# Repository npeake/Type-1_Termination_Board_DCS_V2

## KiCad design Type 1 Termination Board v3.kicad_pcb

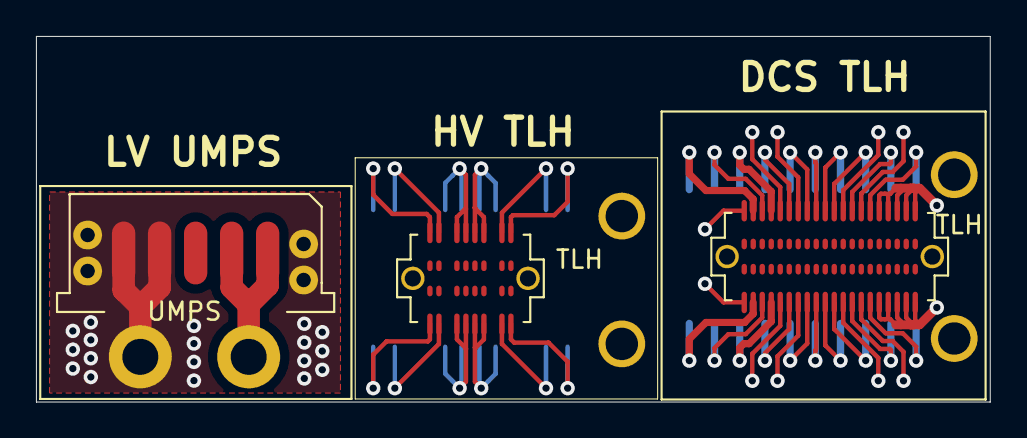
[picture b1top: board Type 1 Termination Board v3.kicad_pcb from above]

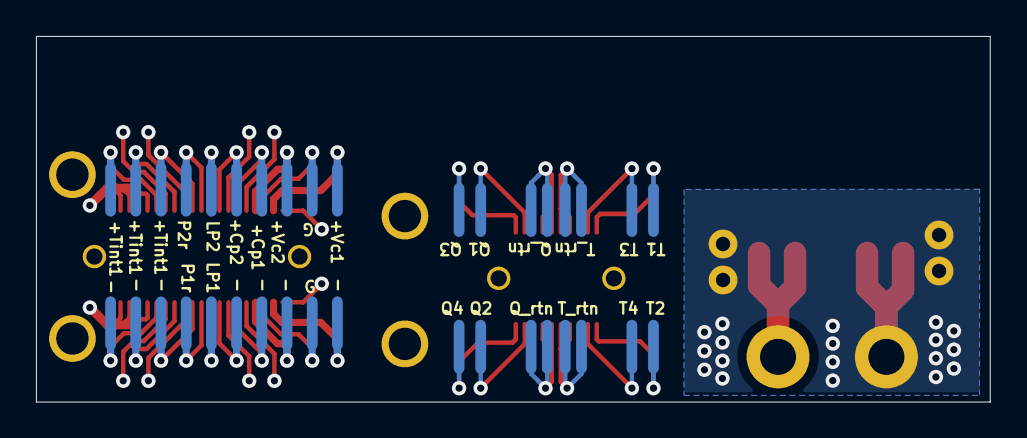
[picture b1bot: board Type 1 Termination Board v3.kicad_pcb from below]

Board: 4 copper layers, 53.0 x 20.3 mm, 13 parts (4 on the bottom side), 3 nets.

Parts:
J2, J3: Conn_01x01_Female; 14AWG_THT
J10: UMPS; UMPS 5 Pin
J11: TLH; 19-1_TLH_HV
J12: TLH; TLH 20 Pin
J20, J21, J22, J23: PEEK_screw
P1, P2, P3, P4: Pad_Array_2

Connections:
/LV: J2.1, J10.1, J10.2
/return: J3.1, J10.4, J10.5, J10.6, J10.7, J10.8, J10.9
GND: J10.3, J12.1, J12.2, J12.5, J12.6, J12.9, J12.10, J12.13, J12.14, J12.19, J12.20, J12.23, J12.24, J12.27, J12.28, J12.31, J12.32, J12.33, J12.34, J12.35, J12.36, J12.37, J12.38, J12.39, J12.40, J12.41, J12.42, J22.43, J23.44, P1.6, P1.20, P2.5, P2.19

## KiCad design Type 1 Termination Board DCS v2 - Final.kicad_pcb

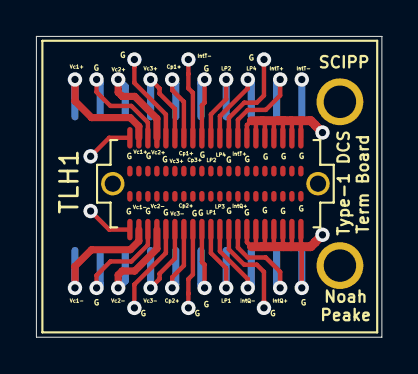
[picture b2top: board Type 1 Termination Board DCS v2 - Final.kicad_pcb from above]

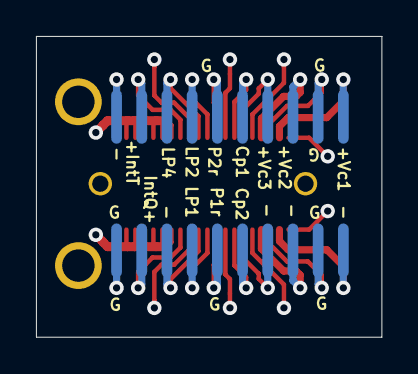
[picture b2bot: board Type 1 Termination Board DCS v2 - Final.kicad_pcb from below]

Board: 4 copper layers, 19.2 x 16.7 mm, 5 parts (2 on the bottom side), 16 nets.

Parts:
J22, J23: PEEK_screw
P1, P2: Pad_Array_2
TLH1: Conn_02x20_Odd_Even; TLH 20 Pin

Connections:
Can_pwr1: P2.15, TLH1.13
Can_pwr2: P1.16, TLH1.14
Can_pwr3: P2.29, TLH1.15
Gnd: J22.43, J23.44, P1.6, P1.18, P1.30, P2.5, P2.17, TLH1.1, TLH1.2, TLH1.5, TLH1.6, TLH1.9, TLH1.10, TLH1.16, TLH1.17, TLH1.18, TLH1.23, TLH1.24, TLH1.27, TLH1.28, TLH1.29, TLH1.30, TLH1.31, TLH1.32, TLH1.33, TLH1.34, TLH1.35, TLH1.36, TLH1.37, TLH1.38, TLH1.39, TLH1.40
Interlock_Q+: P1.26, TLH1.26
Interlock_T+: P2.25, TLH1.25
LP_mode1: P1.20, TLH1.20
LP_mode2: P2.19, TLH1.19
LP_mode3: P1.22, TLH1.22
LP_mode4: P2.21, TLH1.21
Vcan1+: P2.3, TLH1.3
Vcan1-: P1.4, TLH1.4
Vcan2+: P2.7, TLH1.7
Vcan2-: P1.8, TLH1.8
Vcan3+: P2.11, TLH1.11
Vcan3-: P1.12, TLH1.12
